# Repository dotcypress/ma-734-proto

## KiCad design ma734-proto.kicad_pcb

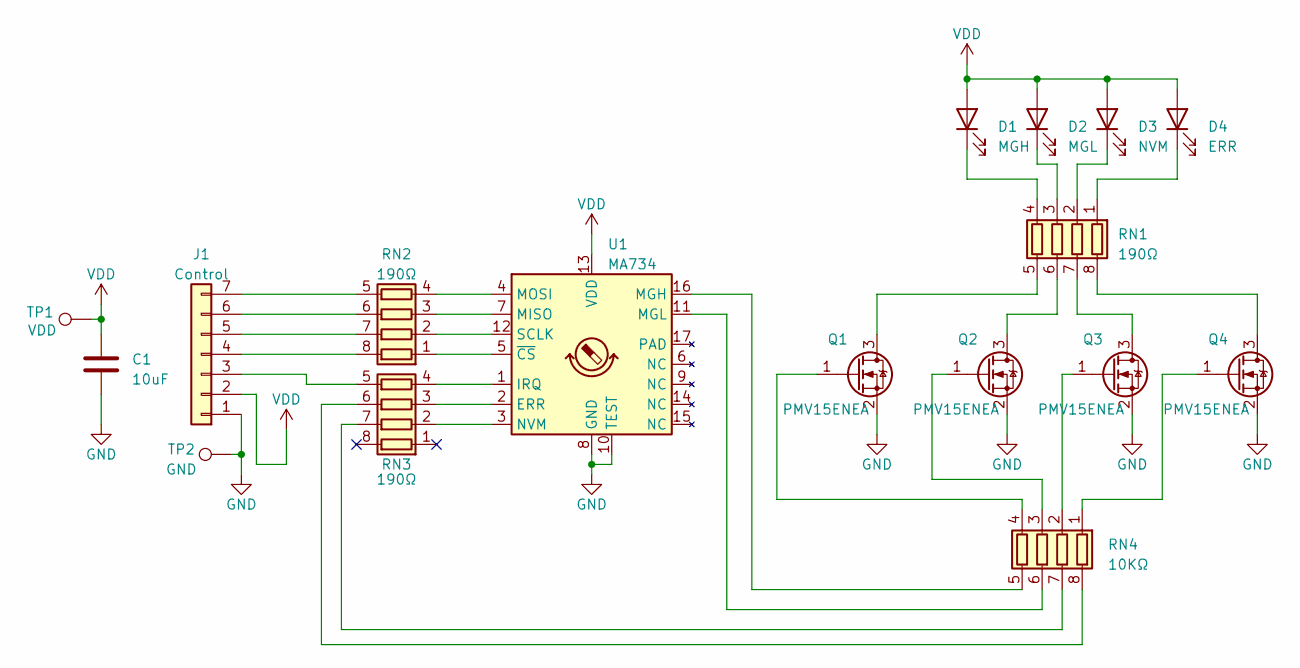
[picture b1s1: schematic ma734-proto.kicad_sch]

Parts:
C1: 10uF; C_0603_1608Metric
D1: MGH; LED_0603_1608Metric
D2: MGL; LED_0603_1608Metric
D3: NVM; LED_0603_1608Metric
D4: ERR; LED_0603_1608Metric
J1: Control; JST_SH_SM07B-SRSS-TB_1x07-1MP_P1.00mm_Horizontal
Q1, Q2, Q3, Q4: PMV15ENEA; SOT-23
RN1, RN2, RN3: 190Ω; R_Array_Convex_4x0603
RN4: 10KΩ; R_Array_Convex_4x0603
TP1: VDD; TestPoint_Pad_D2.0mm
TP2: GND; TestPoint_Pad_2.0x2.0mm
U1: MA734; QFN-16-1EP_3x3mm_P0.5mm_EP1.75x1.75mm

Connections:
GND: C1.2, J1.1, Q1.2 (S), Q2.2 (S), Q3.2 (S), Q4.2 (S), TP2.1, U1.8 (GND), U1.10 (TEST)
unnamed: D1.1 (K), RN1.4 (R4.1)
unnamed: D2.1 (K), RN1.3 (R3.1)
unnamed: D3.1 (K), RN1.2 (R2.1)
unnamed: D4.1 (K), RN1.1 (R1.1)
unnamed: J1.3, RN3.5 (R4.2)
unnamed: J1.4, RN2.8 (R1.2)
unnamed: J1.5, RN2.7 (R2.2)
unnamed: J1.6, RN2.6 (R3.2)
unnamed: J1.7, RN2.5 (R4.2)
unnamed: Q1.3 (D), RN1.5 (R4.2)
unnamed: Q1.1 (G), RN4.4 (R4.1)
unnamed: Q2.3 (D), RN1.6 (R3.2)
unnamed: Q2.1 (G), RN4.3 (R3.1)
unnamed: Q3.3 (D), RN1.7 (R2.2)
unnamed: Q3.1 (G), RN4.2 (R2.1)
unnamed: Q4.3 (D), RN1.8 (R1.2)
unnamed: Q4.1 (G), RN4.1 (R1.1)
unnamed: RN2.1 (R1.1), U1.5 (~CS)
unnamed: RN2.2 (R2.1), U1.12 (SCLK)
unnamed: RN2.3 (R3.1), U1.7 (MISO)
unnamed: RN2.4 (R4.1), U1.4 (MOSI)
unnamed: RN3.2 (R2.1), U1.3 (NVM)
unnamed: RN3.7 (R2.2), RN4.7 (R2.2)
unnamed: RN3.3 (R3.1), U1.2 (ERR)
unnamed: RN3.6 (R3.2), RN4.8 (R1.2)
unnamed: RN3.4 (R4.1), U1.1 (IRQ)
unnamed: RN4.6 (R3.2), U1.11 (MGL)
unnamed: RN4.5 (R4.2), U1.16 (MGH)
VDD: C1.1, D1.2 (A), D2.2 (A), D3.2 (A), D4.2 (A), J1.2, TP1.1, U1.13 (VDD)

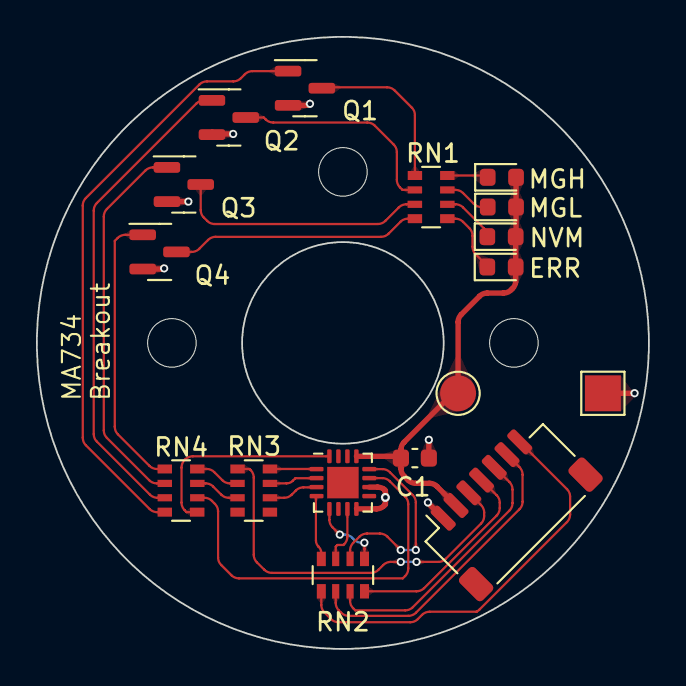
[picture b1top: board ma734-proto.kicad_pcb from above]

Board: 2 copper layers, 34.0 x 34.0 mm, 17 parts (0 on the bottom side), 30 nets.

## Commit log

2023-03-11 rev:0x01
